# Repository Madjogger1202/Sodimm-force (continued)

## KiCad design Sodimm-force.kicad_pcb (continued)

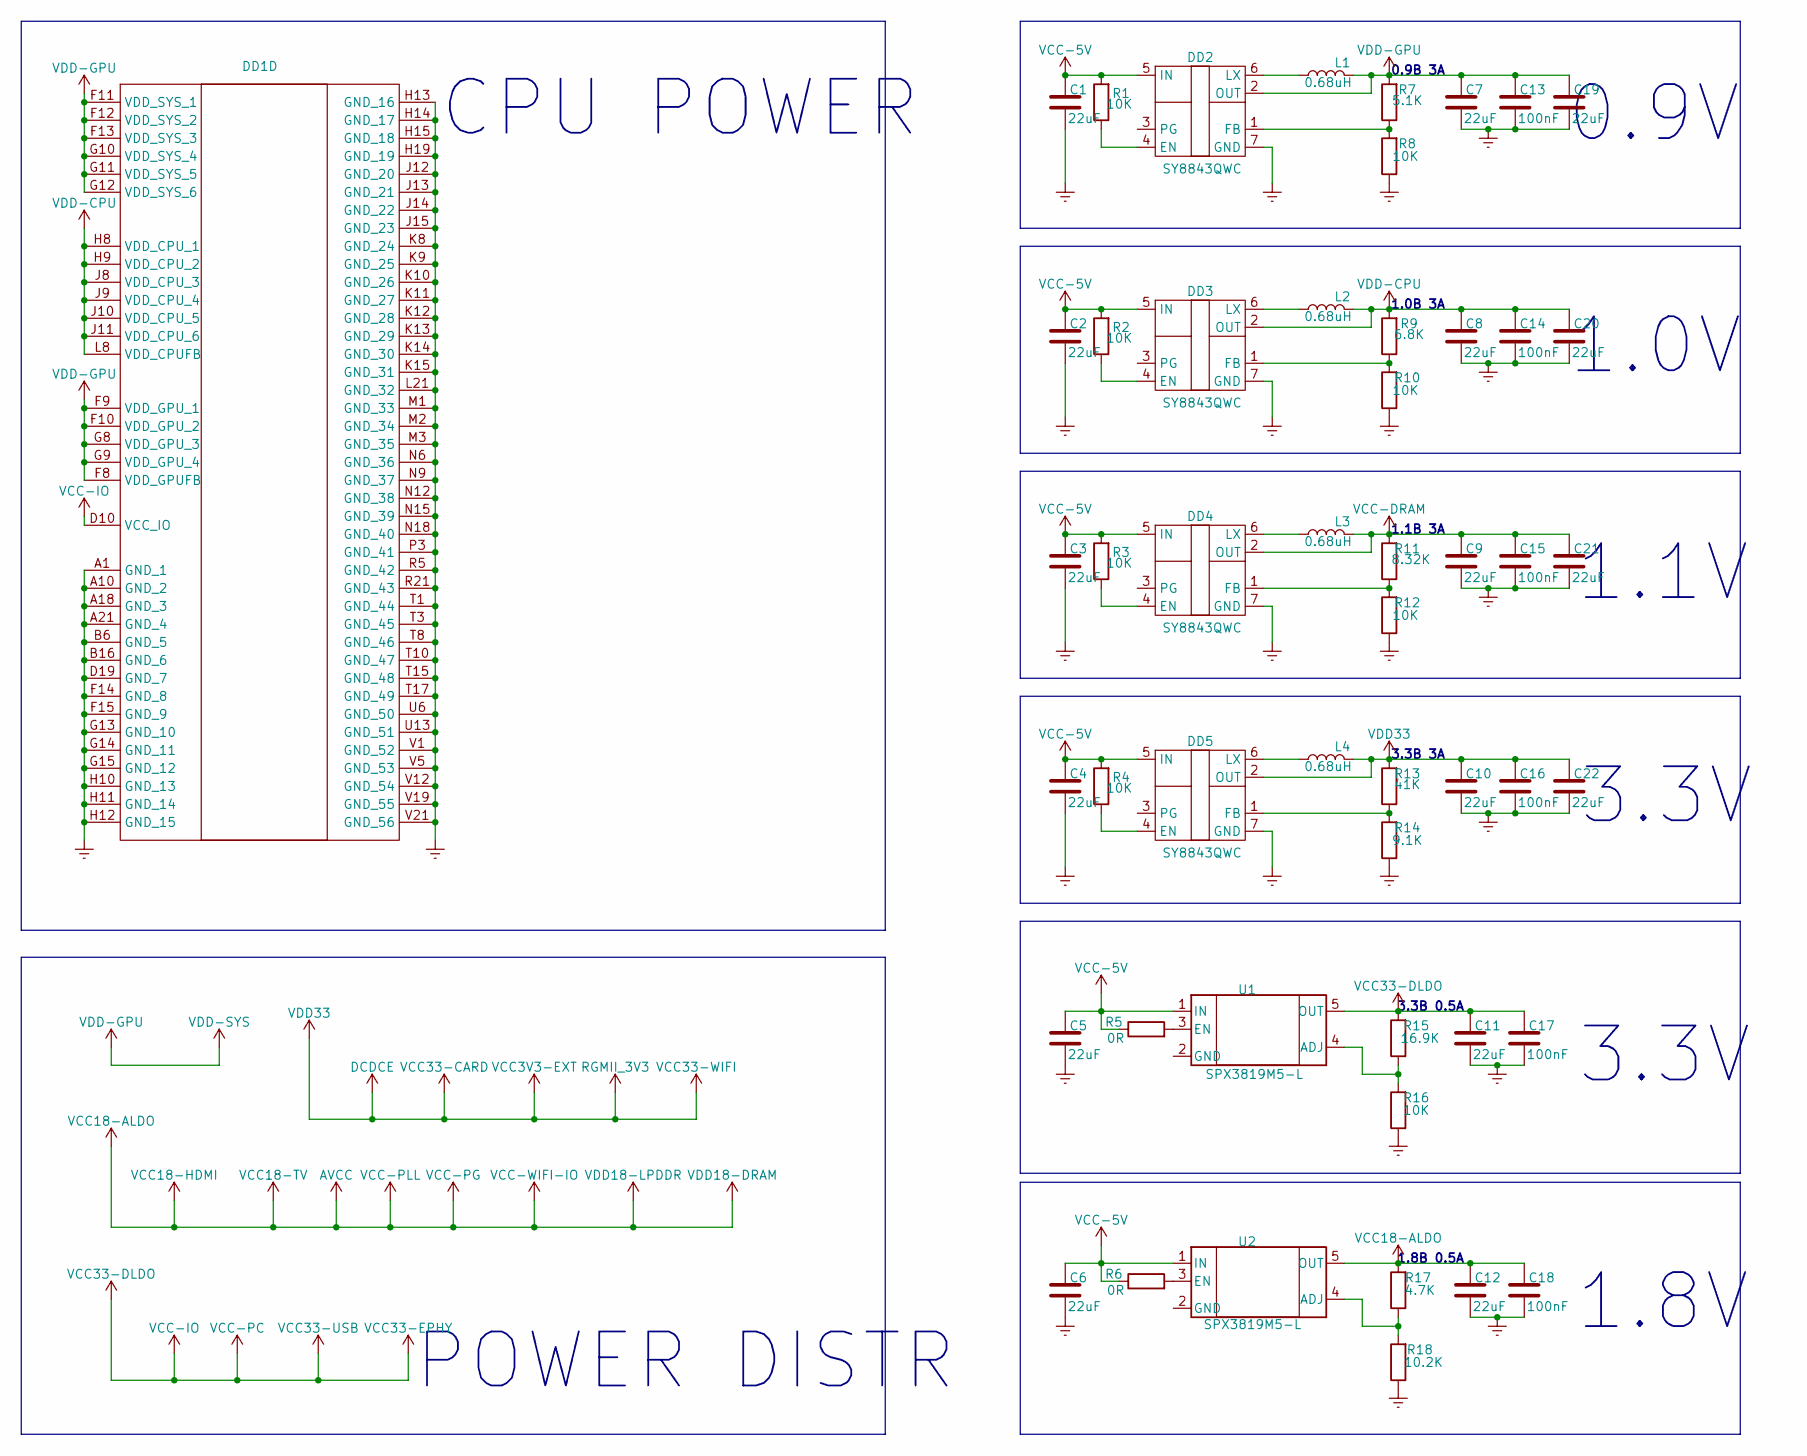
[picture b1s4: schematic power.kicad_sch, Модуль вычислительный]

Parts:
C1, C2, C3, C4, C5, C6, C7, C8, C9, C10, C11, C12, C19, C20, C21, C22: 22uF; C_0402_1005Metric
C13, C14, C15, C16, C17, C18: 100nF; C_0402_1005Metric
DD1: H616
DD2, DD3, DD4, DD5: SY8843QWC
L1, L2, L3, L4: 0.68uH; L_Cenker_CKCS4020
R1, R2, R3, R4, R8, R10, R12: 10K; R_0402_1005Metric
R5, R6: 0R; R_0402_1005Metric
R7: 5.1К; R_0402_1005Metric
R9: 6.8К; R_0402_1005Metric
R11: 8.32К; R_0402_1005Metric
R13: 41К; R_0402_1005Metric
R14: 9.1K; R_0402_1005Metric
R15: 16.9К; R_0402_1005Metric
R16: 10К; R_0402_1005Metric
R17: 4.7К; R_0402_1005Metric
R18: 10.2К; R_0402_1005Metric
U1, U2: SPX3819M5-L; SOT-23-5

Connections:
AVCC: C12.1, C18.1, R17.2, U2.5 (OUT); also elsewhere on the board
DCDCE: C10.1, C16.1, C22.1, DD5.2 (OUT), L4.2, R13.2; also elsewhere on the board
Earth: C1.2, C2.2, C3.2, C4.2, C5.2, C6.2, C7.2, C8.2, C9.2, C10.2, C11.2, C12.2, C13.2, C14.2, C15.2, C16.2, C17.2, C18.2, C19.2, C20.2, C21.2, C22.2, DD1.A1 (GND_1), DD1.A10 (GND_2), DD1.A18 (GND_3), DD1.A21 (GND_4), DD1.B6 (GND_5), DD1.B16 (GND_6), DD1.D19 (GND_7), DD1.F14 (GND_8), DD1.F15 (GND_9), DD1.G13 (GND_10), DD1.G14 (GND_11), DD1.G15 (GND_12), DD1.H10 (GND_13), DD1.H11 (GND_14), DD1.H12 (GND_15), DD1.H13 (GND_16), DD1.H14 (GND_17), DD1.H15 (GND_18), DD1.H19 (GND_19), DD1.J12 (GND_20), DD1.J13 (GND_21), DD1.J14 (GND_22), DD1.J15 (GND_23), DD1.K8 (GND_24), DD1.K9 (GND_25), DD1.K10 (GND_26), DD1.K11 (GND_27), DD1.K12 (GND_28), DD1.K13 (GND_29), DD1.K14 (GND_30), DD1.K15 (GND_31), DD1.L21 (GND_32), DD1.M1 (GND_33), DD1.M2 (GND_34), DD1.M3 (GND_35), DD1.N6 (GND_36), DD1.N9 (GND_37), DD1.N12 (GND_38), DD1.N15 (GND_39), DD1.N18 (GND_40), DD1.P3 (GND_41), DD1.R5 (GND_42), DD1.R21 (GND_43), DD1.T1 (GND_44), DD1.T3 (GND_45), DD1.T8 (GND_46), DD1.T10 (GND_47), DD1.T15 (GND_48), DD1.T17 (GND_49), DD1.U6 (GND_50), DD1.U13 (GND_51), DD1.V1 (GND_52), DD1.V5 (GND_53), DD1.V12 (GND_54), DD1.V19 (GND_55), DD1.V21 (GND_56), DD2.7 (GND), DD3.7 (GND), DD4.7 (GND), DD5.7 (GND), R8.1, R10.1, R12.1, R14.1, R16.1, R18.1; also elsewhere on the board
unnamed: DD2.4 (EN), R1.1
unnamed: DD2.1 (FB), R7.1, R8.2
unnamed: DD2.6 (LX), L1.1
unnamed: DD3.4 (EN), R2.1
unnamed: DD3.1 (FB), R9.1, R10.2
unnamed: DD3.6 (LX), L2.1
unnamed: DD4.4 (EN), R3.1
unnamed: DD4.1 (FB), R11.1, R12.2
unnamed: DD4.6 (LX), L3.1
unnamed: DD5.4 (EN), R4.1
unnamed: DD5.1 (FB), R13.1, R14.2
unnamed: DD5.6 (LX), L4.1
unnamed: R15.1, R16.2, U1.4 (ADJ)
unnamed: R5.2, U1.3 (EN)
unnamed: R17.1, R18.2, U2.4 (ADJ)
unnamed: R6.2, U2.3 (EN)
VCC-5V: C1.1, C2.1, C3.1, C4.1, C5.1, C6.1, DD2.5 (IN), DD3.5 (IN), DD4.5 (IN), DD5.5 (IN), R1.2, R2.2, R3.2, R4.2, R5.1, R6.1, U1.1 (IN), U2.1 (IN); also elsewhere on the board
VCC-DRAM: C9.1, C15.1, C21.1, DD4.2 (OUT), L3.2, R11.2; also elsewhere on the board
VCC-IO: C11.1, C17.1, DD1.D10 (VCC_IO), R15.2, U1.5 (OUT); also elsewhere on the board
VDD-CPU: C8.1, C14.1, C20.1, DD1.H8 (VDD_CPU_1), DD1.H9 (VDD_CPU_2), DD1.J8 (VDD_CPU_3), DD1.J9 (VDD_CPU_4), DD1.J10 (VDD_CPU_5), DD1.J11 (VDD_CPU_6), DD1.L8 (VDD_CPUFB), DD3.2 (OUT), L2.2, R9.2; also elsewhere on the board
VDD-GPU: C7.1, C13.1, C19.1, DD1.F8 (VDD_GPUFB), DD1.F9 (VDD_GPU_1), DD1.F10 (VDD_GPU_2), DD1.F11 (VDD_SYS_1), DD1.F12 (VDD_SYS_2), DD1.F13 (VDD_SYS_3), DD1.G8 (VDD_GPU_3), DD1.G9 (VDD_GPU_4), DD1.G10 (VDD_SYS_4), DD1.G11 (VDD_SYS_5), DD1.G12 (VDD_SYS_6), DD2.2 (OUT), L1.2, R7.2; also elsewhere on the board

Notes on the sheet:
1.8V
CPU POWER
POWER DISTR
3.3V
1.0В 3А
3.3В 0.5А
0.9V
1.1V
1.8В 0.5А
1.0V
0.9В 3А
3.3В 3А
1.1В 3А

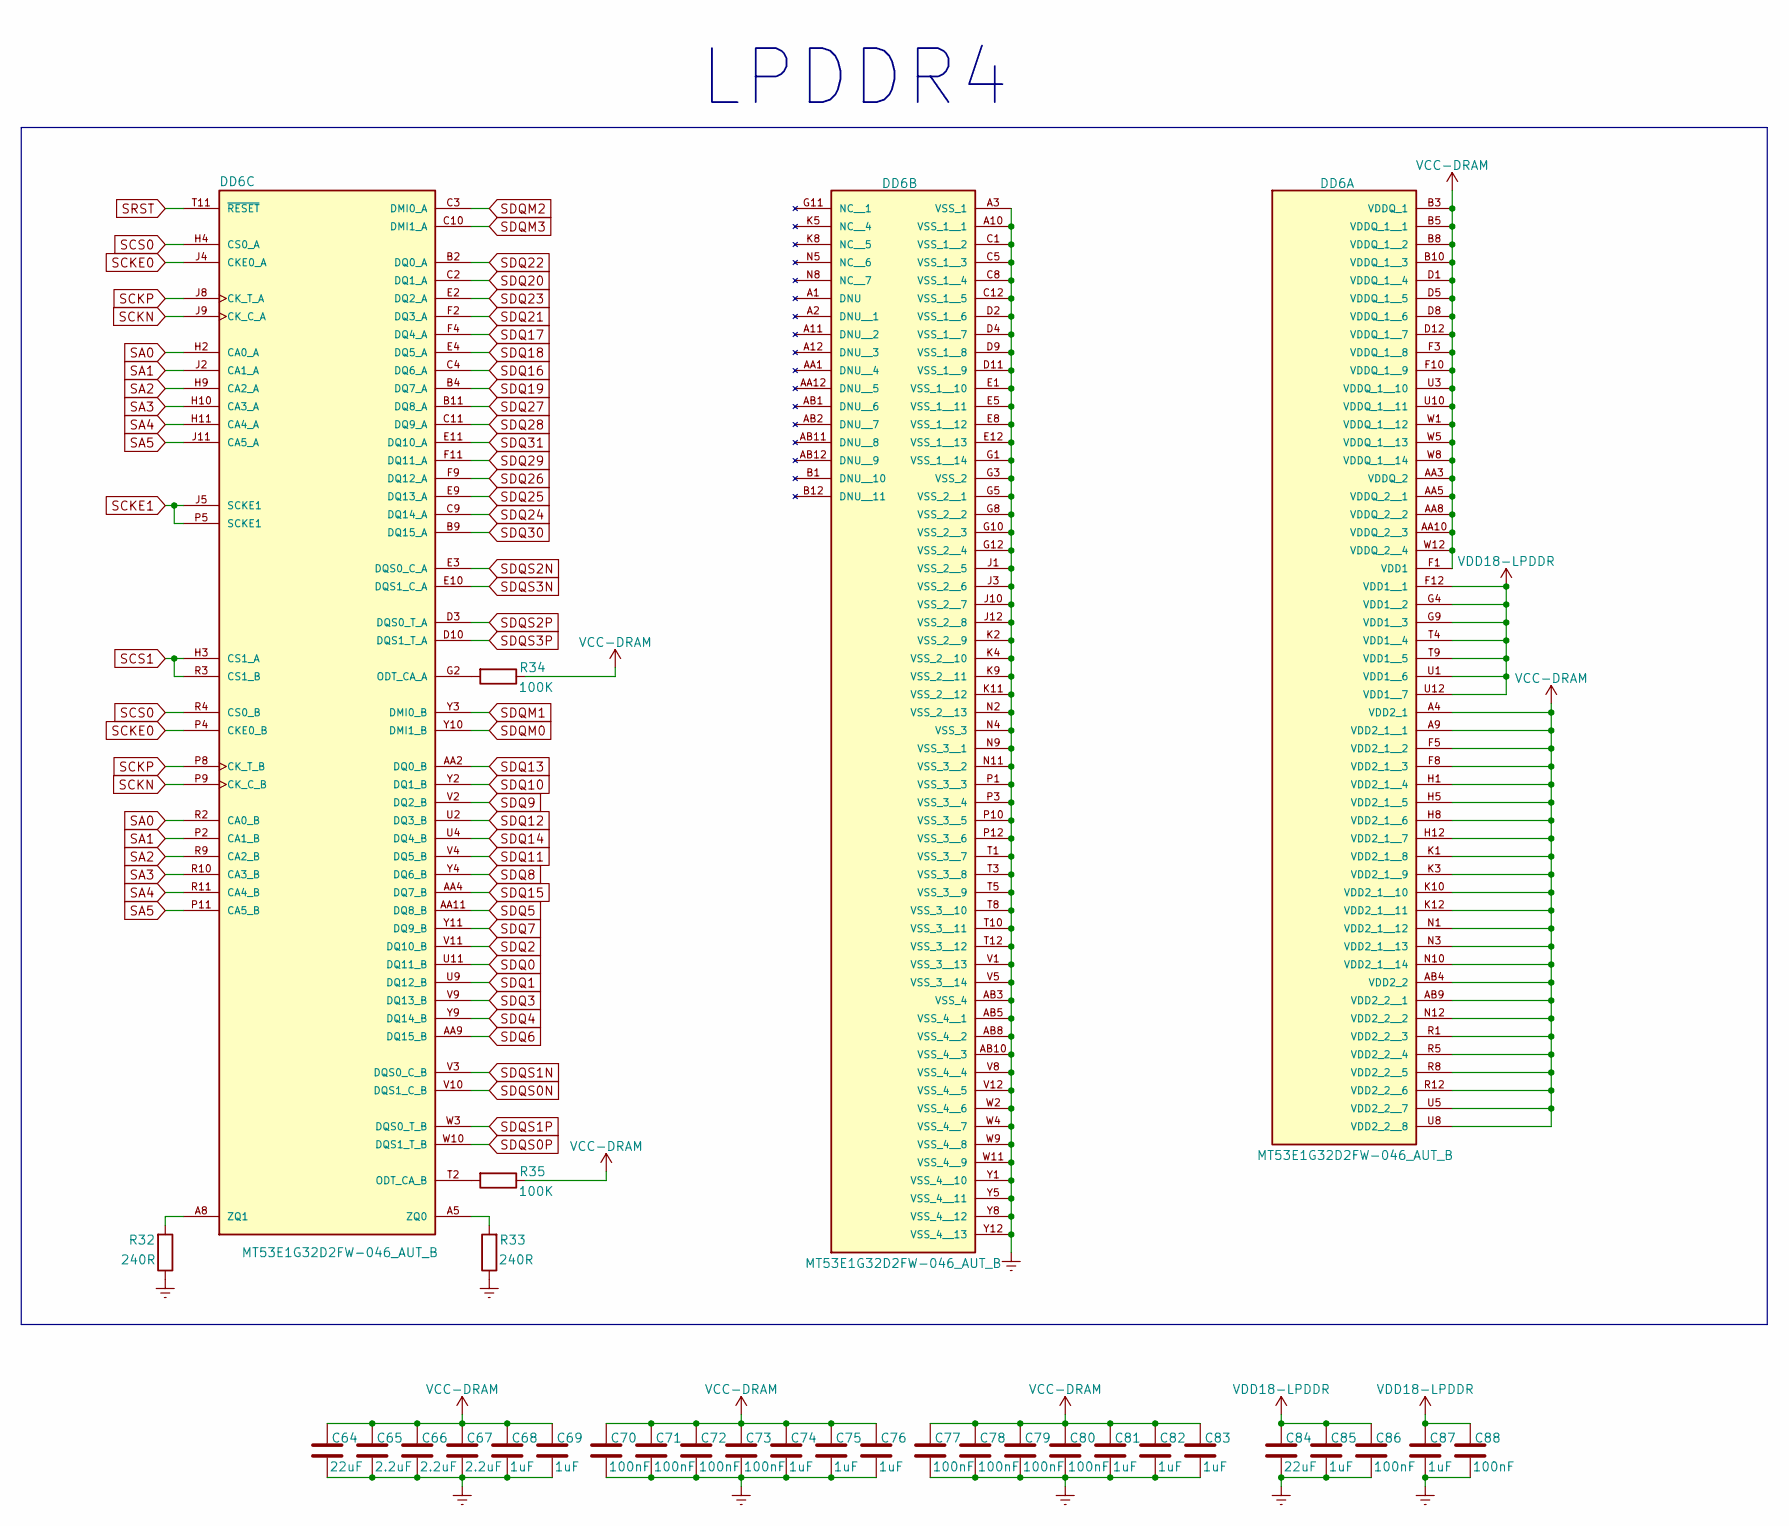
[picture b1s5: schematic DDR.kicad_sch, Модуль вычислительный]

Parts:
C64, C84: 22uF; C_0402_1005Metric
C65, C66, C67: 2.2uF; C_0402_1005Metric
C68, C69, C74, C75, C76, C81, C82, C83, C85, C87: 1uF; C_0402_1005Metric
C70, C71, C72, C73, C77, C78, C79, C80, C86, C88: 100nF; C_0402_1005Metric
DD6: MT53E1G32D2FW-046_AUT_B; BGA200C65X80P22X12_1500X1000X114N
R32, R33: 240R; R_0402_1005Metric
R34, R35: 100K; R_0402_1005Metric

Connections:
AVCC: C84.1, C85.1, C86.1, C87.1, C88.1, DD6.F12 (VDD1__1), DD6.G4 (VDD1__2), DD6.G9 (VDD1__3), DD6.T4 (VDD1__4), DD6.T9 (VDD1__5), DD6.U1 (VDD1__6), DD6.U12 (VDD1__7); also elsewhere on the board
Earth: C64.2, C65.2, C66.2, C67.2, C68.2, C69.2, C70.2, C71.2, C72.2, C73.2, C74.2, C75.2, C76.2, C77.2, C78.2, C79.2, C80.2, C81.2, C82.2, C83.2, C84.2, C85.2, C86.2, C87.2, C88.2, DD6.A3 (VSS_1), DD6.A10 (VSS_1__1), DD6.AB3 (VSS_4), DD6.AB5 (VSS_4__1), DD6.AB8 (VSS_4__2), DD6.AB10 (VSS_4__3), DD6.C1 (VSS_1__2), DD6.C5 (VSS_1__3), DD6.C8 (VSS_1__4), DD6.C12 (VSS_1__5), DD6.D2 (VSS_1__6), DD6.D4 (VSS_1__7), DD6.D9 (VSS_1__8), DD6.D11 (VSS_1__9), DD6.E1 (VSS_1__10), DD6.E5 (VSS_1__11), DD6.E8 (VSS_1__12), DD6.E12 (VSS_1__13), DD6.G1 (VSS_1__14), DD6.G3 (VSS_2), DD6.G5 (VSS_2__1), DD6.G8 (VSS_2__2), DD6.G10 (VSS_2__3), DD6.G12 (VSS_2__4), DD6.J1 (VSS_2__5), DD6.J3 (VSS_2__6), DD6.J10 (VSS_2__7), DD6.J12 (VSS_2__8), DD6.K2 (VSS_2__9), DD6.K4 (VSS_2__10), DD6.K9 (VSS_2__11), DD6.K11 (VSS_2__12), DD6.N2 (VSS_2__13), DD6.N4 (VSS_3), DD6.N9 (VSS_3__1), DD6.N11 (VSS_3__2), DD6.P1 (VSS_3__3), DD6.P3 (VSS_3__4), DD6.P10 (VSS_3__5), DD6.P12 (VSS_3__6), DD6.T1 (VSS_3__7), DD6.T3 (VSS_3__8), DD6.T5 (VSS_3__9), DD6.T8 (VSS_3__10), DD6.T10 (VSS_3__11), DD6.T12 (VSS_3__12), DD6.V1 (VSS_3__13), DD6.V5 (VSS_3__14), DD6.V8 (VSS_4__4), DD6.V12 (VSS_4__5), DD6.W2 (VSS_4__6), DD6.W4 (VSS_4__7), DD6.W9 (VSS_4__8), DD6.W11 (VSS_4__9), DD6.Y1 (VSS_4__10), DD6.Y5 (VSS_4__11), DD6.Y8 (VSS_4__12), DD6.Y12 (VSS_4__13), R32.1, R33.1; also elsewhere on the board
unnamed: DD6.G2 (ODT_CA_A), R34.2
unnamed: DD6.T2 (ODT_CA_B), R35.2
unnamed: DD6.A5 (ZQ0), R33.2
unnamed: DD6.A8 (ZQ1), R32.2
SA0: DD6.H2 (CA0_A), DD6.R2 (CA0_B); also elsewhere on the board
SA1: DD6.J2 (CA1_A), DD6.P2 (CA1_B); also elsewhere on the board
SA2: DD6.H9 (CA2_A), DD6.R9 (CA2_B); also elsewhere on the board
SA3: DD6.H10 (CA3_A), DD6.R10 (CA3_B); also elsewhere on the board
SA4: DD6.H11 (CA4_A), DD6.R11 (CA4_B); also elsewhere on the board
SA5: DD6.J11 (CA5_A), DD6.P11 (CA5_B); also elsewhere on the board
SCKE0: DD6.J4 (CKE0_A), DD6.P4 (CKE0_B); also elsewhere on the board
SCKE1: DD6.J5 (SCKE1), DD6.P5 (SCKE1); also elsewhere on the board
SCKN: DD6.J9 (CK_C_A), DD6.P9 (CK_C_B); also elsewhere on the board
SCKP: DD6.J8 (CK_T_A), DD6.P8 (CK_T_B); also elsewhere on the board
SCS0: DD6.H4 (CS0_A), DD6.R4 (CS0_B); also elsewhere on the board
SCS1: DD6.H3 (CS1_A), DD6.R3 (CS1_B); also elsewhere on the board
SDQ0: DD6.U11 (DQ11_B); also elsewhere on the board
SDQ1: DD6.U9 (DQ12_B); also elsewhere on the board
SDQ2: DD6.V11 (DQ10_B); also elsewhere on the board
SDQ3: DD6.V9 (DQ13_B); also elsewhere on the board
SDQ4: DD6.Y9 (DQ14_B); also elsewhere on the board
SDQ5: DD6.AA11 (DQ8_B); also elsewhere on the board
SDQ6: DD6.AA9 (DQ15_B); also elsewhere on the board
SDQ7: DD6.Y11 (DQ9_B); also elsewhere on the board
SDQ8: DD6.Y4 (DQ6_B); also elsewhere on the board
SDQ9: DD6.V2 (DQ2_B); also elsewhere on the board
SDQ10: DD6.Y2 (DQ1_B); also elsewhere on the board
SDQ11: DD6.V4 (DQ5_B); also elsewhere on the board
SDQ12: DD6.U2 (DQ3_B); also elsewhere on the board
SDQ13: DD6.AA2 (DQ0_B); also elsewhere on the board
SDQ14: DD6.U4 (DQ4_B); also elsewhere on the board
SDQ15: DD6.AA4 (DQ7_B); also elsewhere on the board
SDQ16: DD6.C4 (DQ6_A); also elsewhere on the board
SDQ17: DD6.F4 (DQ4_A); also elsewhere on the board
SDQ18: DD6.E4 (DQ5_A); also elsewhere on the board
SDQ19: DD6.B4 (DQ7_A); also elsewhere on the board
SDQ20: DD6.C2 (DQ1_A); also elsewhere on the board
SDQ21: DD6.F2 (DQ3_A); also elsewhere on the board
SDQ22: DD6.B2 (DQ0_A); also elsewhere on the board
SDQ23: DD6.E2 (DQ2_A); also elsewhere on the board
SDQ24: DD6.C9 (DQ14_A); also elsewhere on the board
SDQ25: DD6.E9 (DQ13_A); also elsewhere on the board
SDQ26: DD6.F9 (DQ12_A); also elsewhere on the board
SDQ27: DD6.B11 (DQ8_A); also elsewhere on the board
SDQ28: DD6.C11 (DQ9_A); also elsewhere on the board
SDQ29: DD6.F11 (DQ11_A); also elsewhere on the board
SDQ30: DD6.B9 (DQ15_A); also elsewhere on the board
SDQ31: DD6.E11 (DQ10_A); also elsewhere on the board
SDQM0: DD6.Y10 (DMI1_B); also elsewhere on the board
SDQM1: DD6.Y3 (DMI0_B); also elsewhere on the board
SDQM2: DD6.C3 (DMI0_A); also elsewhere on the board
SDQM3: DD6.C10 (DMI1_A); also elsewhere on the board
SDQS0N: DD6.V10 (DQS1_C_B); also elsewhere on the board
SDQS0P: DD6.W10 (DQS1_T_B); also elsewhere on the board
SDQS1N: DD6.V3 (DQS0_C_B); also elsewhere on the board
SDQS1P: DD6.W3 (DQS0_T_B); also elsewhere on the board
SDQS2N: DD6.E3 (DQS0_C_A); also elsewhere on the board
SDQS2P: DD6.D3 (DQS0_T_A); also elsewhere on the board
SDQS3N: DD6.E10 (DQS1_C_A); also elsewhere on the board
SDQS3P: DD6.D10 (DQS1_T_A); also elsewhere on the board
SRST: DD6.T11 (~RESET); also elsewhere on the board
VCC-DRAM: C64.1, C65.1, C66.1, C67.1, C68.1, C69.1, C70.1, C71.1, C72.1, C73.1, C74.1, C75.1, C76.1, C77.1, C78.1, C79.1, C80.1, C81.1, C82.1, C83.1, DD6.A4 (VDD2_1), DD6.A9 (VDD2_1__1), DD6.AA3 (VDDQ_2), DD6.AA5 (VDDQ_2__1), DD6.AA8 (VDDQ_2__2), DD6.AA10 (VDDQ_2__3), DD6.AB4 (VDD2_2), DD6.AB9 (VDD2_2__1), DD6.B3 (VDDQ_1), DD6.B5 (VDDQ_1__1), DD6.B8 (VDDQ_1__2), DD6.B10 (VDDQ_1__3), DD6.D1 (VDDQ_1__4), DD6.D5 (VDDQ_1__5), DD6.D8 (VDDQ_1__6), DD6.D12 (VDDQ_1__7), DD6.F1 (VDD1), DD6.F3 (VDDQ_1__8), DD6.F5 (VDD2_1__2), DD6.F8 (VDD2_1__3), DD6.F10 (VDDQ_1__9), DD6.H1 (VDD2_1__4), DD6.H5 (VDD2_1__5), DD6.H8 (VDD2_1__6), DD6.H12 (VDD2_1__7), DD6.K1 (VDD2_1__8), DD6.K3 (VDD2_1__9), DD6.K10 (VDD2_1__10), DD6.K12 (VDD2_1__11), DD6.N1 (VDD2_1__12), DD6.N3 (VDD2_1__13), DD6.N10 (VDD2_1__14), DD6.N12 (VDD2_2__2), DD6.R1 (VDD2_2__3), DD6.R5 (VDD2_2__4), DD6.R8 (VDD2_2__5), DD6.R12 (VDD2_2__6), DD6.U3 (VDDQ_1__10), DD6.U5 (VDD2_2__7), DD6.U8 (VDD2_2__8), DD6.U10 (VDDQ_1__11), DD6.W1 (VDDQ_1__12), DD6.W5 (VDDQ_1__13), DD6.W8 (VDDQ_1__14), DD6.W12 (VDDQ_2__4), R34.1, R35.1; also elsewhere on the board

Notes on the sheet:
LPDDR4

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
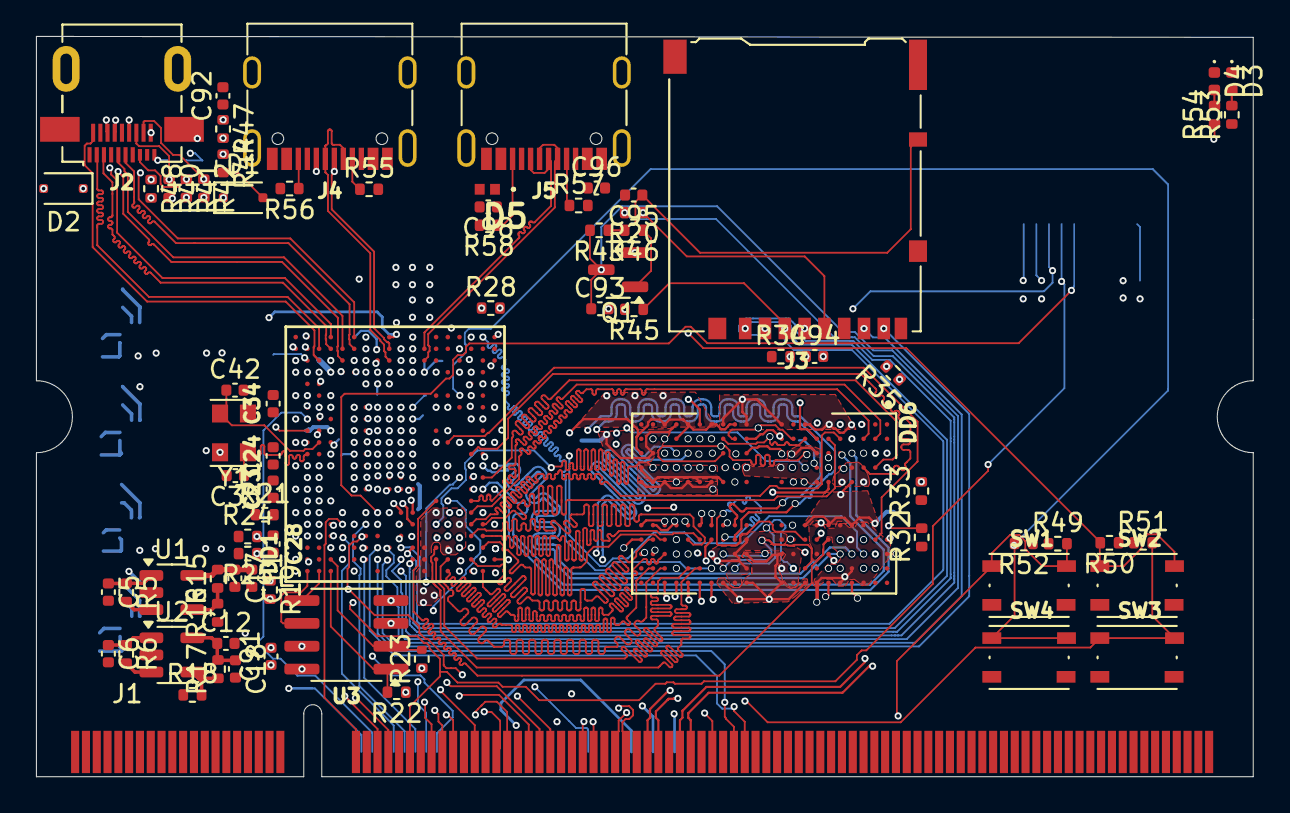
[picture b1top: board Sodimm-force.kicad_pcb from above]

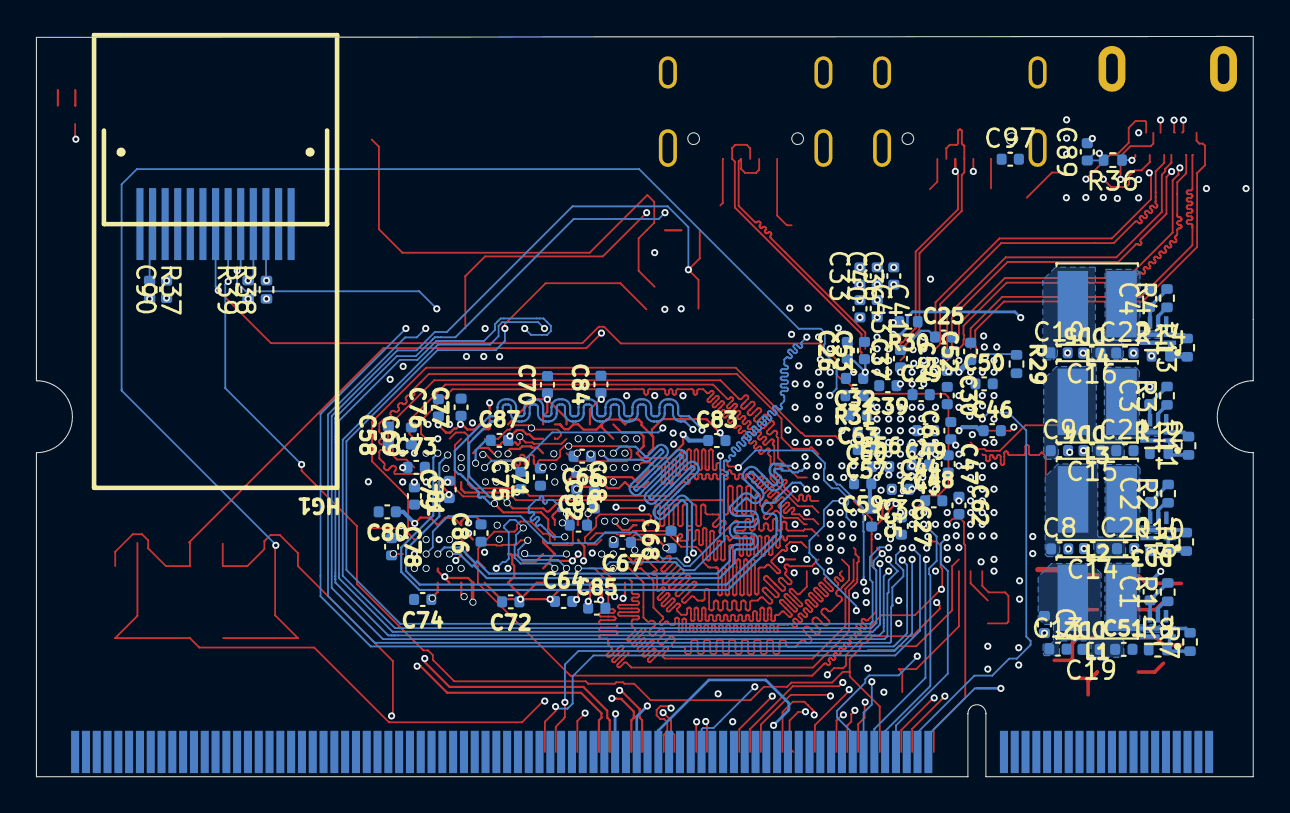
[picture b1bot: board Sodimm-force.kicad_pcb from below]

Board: 8 copper layers, 67.6 x 41.1 mm, 183 parts (106 on the bottom side), 182 nets.

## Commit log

2025-02-09 Initial commit Готова общая структура схемы, заполнены форматки и расставлена часть элементов по схеме
2025-02-10 расставлены основные блоки и компоненты, подобраны компоненты интерфейса и питания
2025-02-12 Внесены распиновки интерфейсного модуля и модуля GPIO + конденсаторы по питанию 2/7 референсной схемы
2025-02-14 Доработка DDR, питание
2025-02-14 Обновлена структура, закончен интерфейс, HDMI Завершено проектирование линий питания и подтяжек для интерфейсов
2025-02-17 Схема закончена, часть компонентов расставлена на плате
2025-02-17 Пытаюсь сделать трассировку DDК
2025-02-18 вроде хехе чуть трассировки DDR
2025-02-19 пу-пу-пу
2025-02-20 Добавлены предельные правила
2025-02-24 Трассировка с полными соединениями DDR
2025-02-28 Согласовал по длине 1.5 слоя
2025-03-01 DDR оттрассирована!! 🥹
2025-03-01 Кучка исправлений, переместил SD карту, дисплей, в целом компоновка чуть другая Небольшие исправления в схеме 🤠
2025-03-01 Навёл красоту, убрал подтяжку для питания что скопировал с реф дизайна ( у меня не умные DC-DC ) + компоновка decoupling кондёров и быстрой обвязки чипа
2025-03-09 Проведены все линии данных, осталось лишь сделать полигонами питание и шелкографию исправить :)
2025-03-10 Чаcтичная трассировка питания
2025-03-10 rev0 готова
2025-03-11 Небольшое исправление шелкографии, дозалил остальные слои землёй для понижения общего импеданса
2025-03-11 Добавлен BOM
2025-05-20 Исправление УГО по ГОСТу, добавление 3D моделей
2025-05-22 GOST update
2025-08-05 рефакторинг структуры, проверка Readme
2025-08-05 upd readme
2025-08-05 readme upd
